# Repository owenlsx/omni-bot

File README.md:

# Omni Robot PCB

KiCad project for the Omni-directional robot.

## Contents
- Schematic: Omni_robot.kicad_sch
- PCB layout: Omni_robot.kicad_pcb

## Notes
- ESP32-S3 based controller
- BMX055 IMU
- 1S LiPo power system

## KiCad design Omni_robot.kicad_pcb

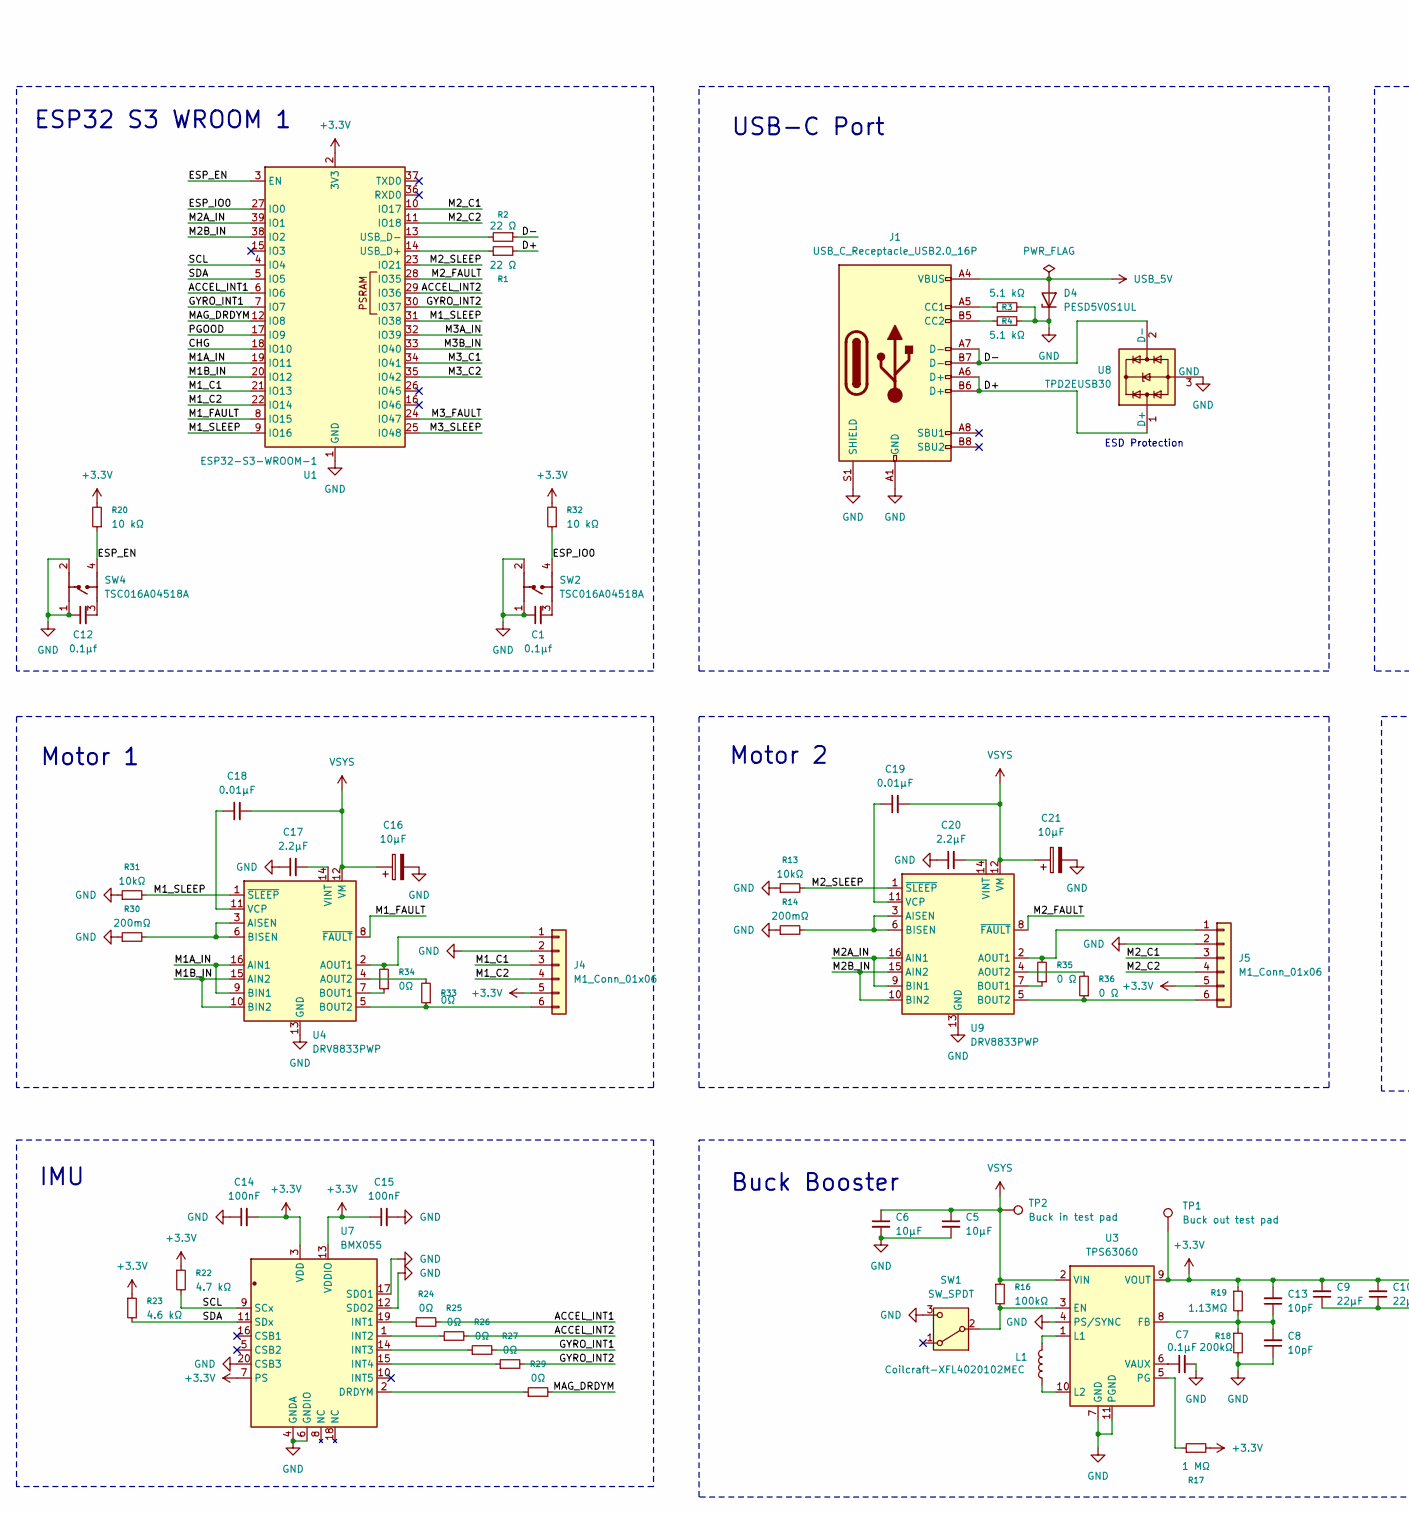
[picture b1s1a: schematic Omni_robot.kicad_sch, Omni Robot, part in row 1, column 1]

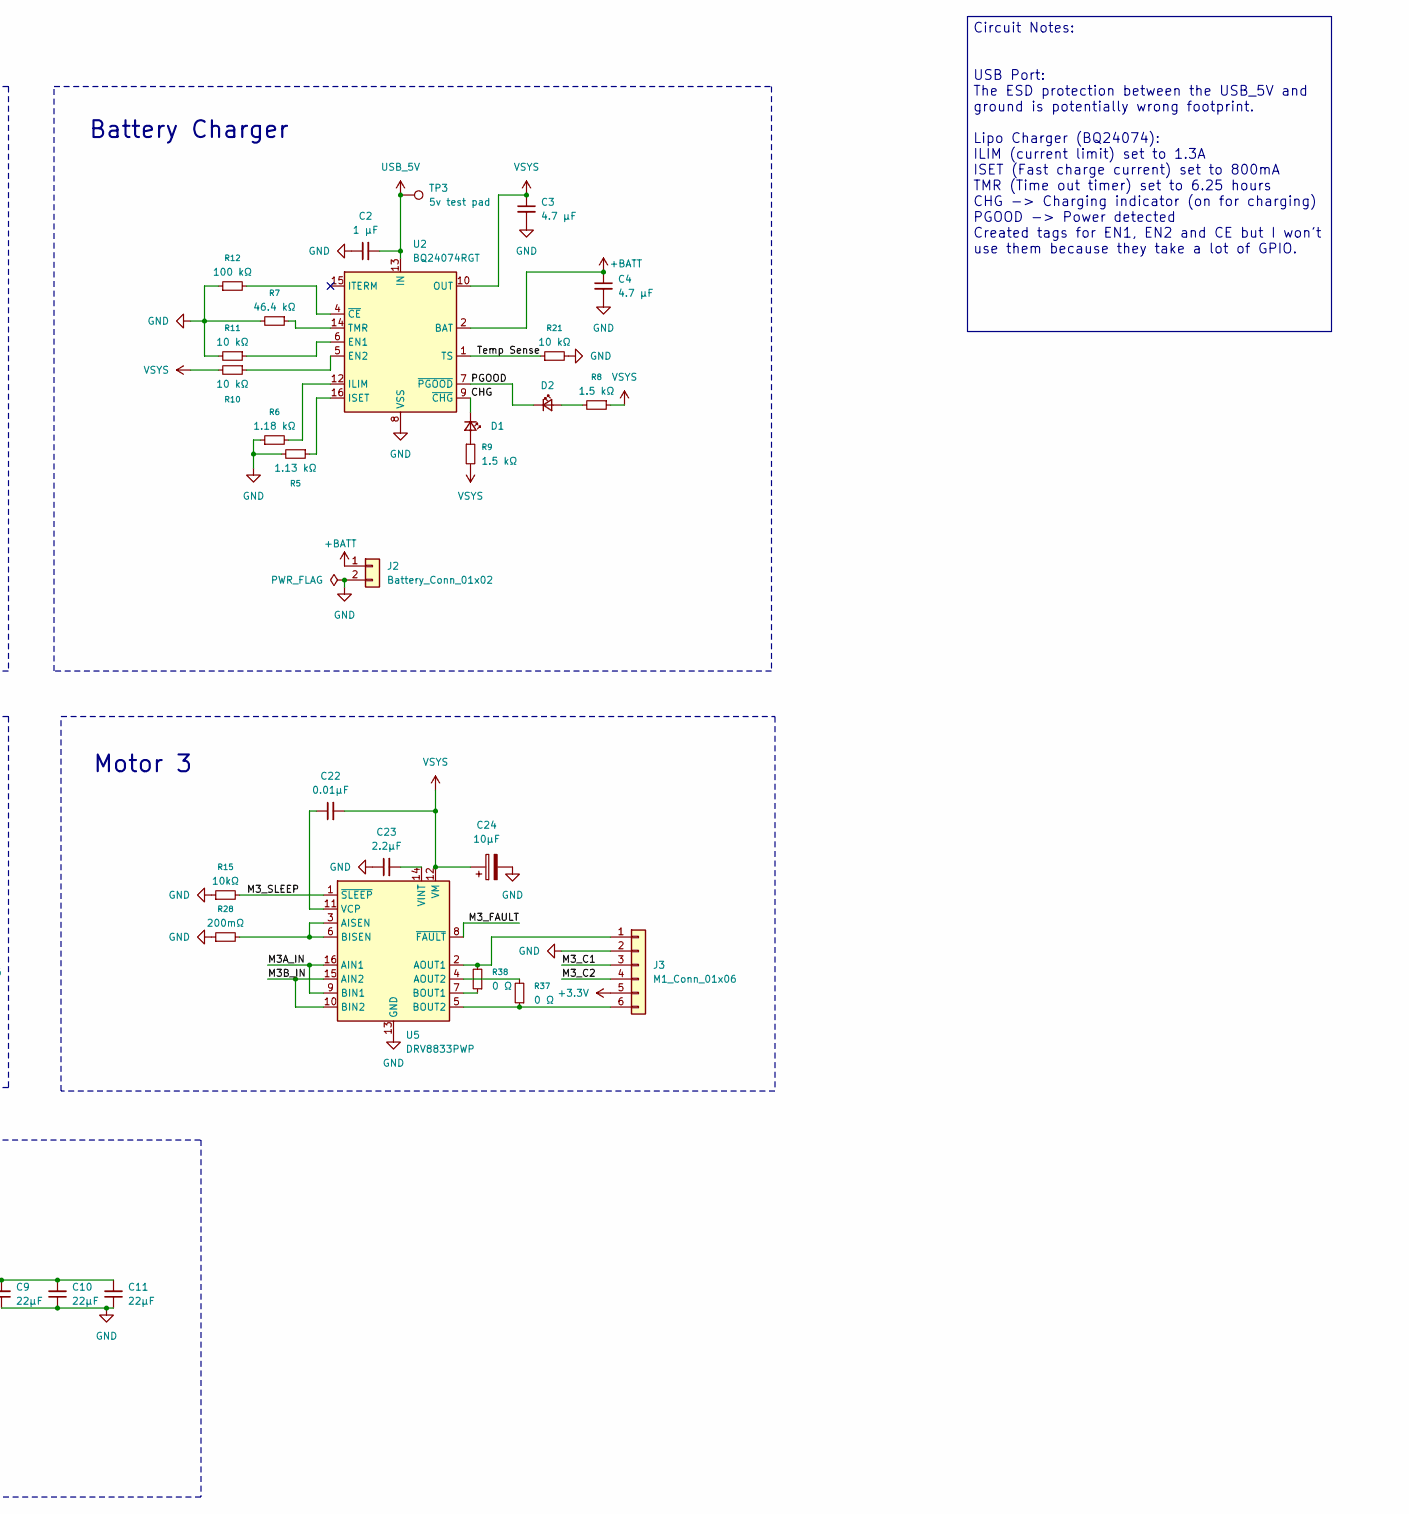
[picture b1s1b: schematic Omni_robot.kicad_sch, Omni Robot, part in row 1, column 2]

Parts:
C1, C12: 0.1µf; C_0603_1608Metric
C2: 1 µF; C_0603_1608Metric
C3, C4: 4.7 µF; C_0603_1608Metric
C5, C6, C16: 10µF; C_0603_1608Metric
C7: 0.1µF; C_0603_1608Metric
C8, C13: 10pF; C_0603_1608Metric
C9, C10, C11: 22µF; C_0603_1608Metric
C14, C15: 100nF; C_0603_1608Metric
C17: 2.2µF; C_0603_1608Metric
C18: 0.01µF; C_0603_1608Metric
C19, C22: 0.01µF; R_0603_1608Metric
C20, C23: 2.2µF; R_0603_1608Metric
C21, C24: 10µF; R_0603_1608Metric
D1, D2: LED_Small; R_0603_1608Metric
D4: PESD5V0S1UL; R_0603_1608Metric
J1: USB_C_Receptacle_USB2.0_16P; USB_C_Receptacle_Palconn_UTC16-G
J2: Battery_Conn_01x02; JST_PH_B2B-PH-K_1x02_P2.00mm_Vertical
J3, J4, J5: M1_Conn_01x06; JST_GH_BM06B-GHS-TBT_1x06-1MP_P1.25mm_Vertical
L1: Coilcraft-XFL4020102MEC; L_Coilcraft_XAL4020-XXX
R1, R2: 22 Ω; R_0603_1608Metric
R3, R4: 5.1 kΩ; R_0603_1608Metric
R5: 1.13 kΩ; R_0603_1608Metric
R6: 1.18 kΩ; R_0603_1608Metric
R7: 46.4 kΩ; R_0603_1608Metric
R8, R9: 1.5 kΩ; R_0603_1608Metric
R10, R11, R20, R21, R32: 10 kΩ; R_0603_1608Metric
R12: 100 kΩ; R_0603_1608Metric
R13, R15, R31: 10kΩ; R_0603_1608Metric
R14, R28, R30: 200mΩ; R_0603_1608Metric
R16: 100kΩ; R_0603_1608Metric
R17: 1 MΩ; R_0603_1608Metric
R18: 200kΩ; R_0603_1608Metric
R19: 1.13MΩ; R_0603_1608Metric
R22: 4.7 kΩ; R_0603_1608Metric
R23: 4.6 kΩ; R_0603_1608Metric
R24, R25, R26, R27, R29, R33, R34: 0Ω; R_0805_2012Metric
R35, R36, R37, R38: 0 Ω; R_0805_2012Metric
SW1: SW_SPDT; SW-TH_SS12D07VG4
SW2, SW4: TSC016A04518A; SW-TH_4P-L4.5-W4.5-P3.00-LS4.8; Manufacturer Part TSC016A04518A
TP1: Buck out test pad; TestPoint_Pad_D3.0mm
TP2: Buck in test pad; TestPoint_Pad_D3.0mm
TP3: 5v test pad; TestPoint_Pad_D3.0mm
U1: ESP32-S3-WROOM-1
U2: BQ24074RGT; VQFN-16-1EP_3x3mm_P0.5mm_EP1.6x1.6mm
U3: TPS63060; Texas_S-PWSON-N10_ThermalVias
U4, U5, U9: DRV8833PWP; HTSSOP-16-1EP_4.4x5mm_P0.65mm_EP3.4x5mm_Mask2.46x2.31mm_The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
U7: BMX055; BMX055_EasyEDA; Manufacturer Part BMX055
U8: TPD2EUSB30; Texas_DRT-3

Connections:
+3.3V: C9.2, C10.2, C11.2, C13.2, C14.2, C15.1, J3.5, J4.5, J5.5, R17.2, R19.1, R20.2, R22.1, R23.1, R32.2, TP1.1, U1.2 (3V3), U3.9 (VOUT), U7.3 (VDD), U7.7 (PS), U7.13 (VDDIO)
+BATT: C4.1, J2.1, U2.2 (BAT), U2.3 (BAT)
/ACCEL_INT1: R24.2, U1.6 (IO6)
/ACCEL_INT2: R25.2, U1.29 (IO36)
/CHG: D1.1 (K), U1.18 (IO10), U2.9 (~CHG)
/D+: J1.A6 (D+), J1.B6 (D+), R1.2, U8.1 (D+)
/D-: J1.A7 (D-), J1.B7 (D-), R2.1, U8.2 (D-)
/ESP_EN: R20.1, SW4.4, U1.3 (EN)
/ESP_IO0: R32.1, SW2.4, U1.27 (IO0)
/GYRO_INT1: R26.2, U1.7 (IO7)
/GYRO_INT2: R27.2, U1.30 (IO37)
/M1A_IN: U1.19 (IO11), U4.9 (BIN1), U4.16 (AIN1)
/M1B_IN: U1.20 (IO12), U4.10 (BIN2), U4.15 (AIN2)
/M1_C1: J4.3, U1.21 (IO13)
/M1_C2: J4.4, U1.22 (IO14)
/M1_FAULT: U1.8 (IO15), U4.8 (~FAULT)
/M1_SLEEP: R31.2, U1.9 (IO16), U1.31 (IO38), U4.1 (~SLEEP)
/M2A_IN: U1.39 (IO1), U9.9 (BIN1), U9.16 (AIN1)
/M2B_IN: U1.38 (IO2), U9.10 (BIN2), U9.15 (AIN2)
/M2_C1: J5.3, U1.10 (IO17)
/M2_C2: J5.4, U1.11 (IO18)
/M2_FAULT: U1.28 (IO35), U9.8 (~FAULT)
/M2_SLEEP: R13.2, U1.23 (IO21), U9.1 (~SLEEP)
/M3A_IN: U1.32 (IO39), U5.9 (BIN1), U5.16 (AIN1)
/M3B_IN: U1.33 (IO40), U5.10 (BIN2), U5.15 (AIN2)
/M3_C1: J3.3, U1.34 (IO41)
/M3_C2: J3.4, U1.35 (IO42)
/M3_FAULT: U1.24 (IO47), U5.8 (~FAULT)
/M3_SLEEP: R15.2, U1.25 (IO48), U5.1 (~SLEEP)
/MAG_DRDYM: R29.2, U1.12 (IO8)
/PGOOD: D2.1 (K), U1.17 (IO9), U2.7 (~PGOOD)
/SCL: R22.2, U1.4 (IO4), U7.9 (SCx)
/SDA: R23.2, U1.5 (IO5), U7.11 (SDx)
/Temp Sense: R21.1, U2.1 (TS)
GND: C1.1, C2.1, C3.2, C4.2, C5.2, C6.2, C7.2, C8.1, C9.1, C10.1, C11.1, C12.1, C14.1, C15.2, C16.2, C17.1, C20.1, C21.2, C23.1, C24.2, D4.1 (K), J1.A1 (GND), J1.A12 (GND), J1.B1 (GND), J1.B12 (GND), J1.S1 (SHIELD), J2.2, J3.2, J4.2, J5.2, R3.2, R4.2, R5.2, R6.1, R7.2, R11.2, R12.1, R13.1, R14.1, R15.1, R18.2, R21.2, R28.1, R30.1, R31.1, SW1.3 (C), SW2.1, SW2.2, SW4.1, SW4.2, U1.1 (GND), U1.40 (GND), U1.41 (GND), U2.8 (VSS), U2.17 (VSS), U3.4 (PS/SYNC), U3.7 (GND), U3.11 (PGND), U4.13 (GND), U4.17 (GND), U5.13 (GND), U5.17 (GND), U7.4 (GNDA), U7.6 (GNDIO), U7.12 (SDO2), U7.17 (SDO1), U7.20 (CSB3), U8.3 (GND), U9.13 (GND), U9.17 (GND)
unnamed: C1.2, SW2.3
unnamed: C12.2, SW4.3
unnamed: D1.2 (A), R9.1
unnamed: D2.2 (A), R8.2
unnamed: J1.A5 (CC1), R3.1
unnamed: J1.B5 (CC2), R4.1
unnamed: J3.1, R38.2, U5.2 (AOUT1)
unnamed: J3.6, R37.1, U5.5 (BOUT2)
unnamed: J4.1, R34.2, U4.2 (AOUT1)
unnamed: J4.6, R33.1, U4.5 (BOUT2)
unnamed: J5.1, R35.2, U9.2 (AOUT1)
unnamed: J5.6, R36.1, U9.5 (BOUT2)
unnamed: R16.2, SW1.2 (B), U3.3 (EN)
unnamed: R1.1, U1.14 (USB_D+)
unnamed: R2.2, U1.13 (USB_D-)
unnamed: R11.1, U2.6 (EN1)
unnamed: R10.1, U2.5 (EN2)
unnamed: R6.2, U2.12 (ILIM)
unnamed: R5.1, U2.16 (ISET)
unnamed: R7.1, U2.14 (TMR)
unnamed: R12.2, U2.4 (~CE)
unnamed: C8.2, C13.1, R18.1, R19.2, U3.8 (FB)
unnamed: L1.2, U3.1 (L1)
unnamed: L1.1, U3.10 (L2)
unnamed: R17.1, U3.5 (PG)
unnamed: C7.1, U3.6 (VAUX)
unnamed: R30.2, U4.3 (AISEN), U4.6 (BISEN)
unnamed: R33.2, U4.4 (AOUT2)
unnamed: R34.1, U4.7 (BOUT1)
unnamed: C18.1, U4.11 (VCP)
unnamed: C17.2, U4.14 (VINT)
unnamed: R28.2, U5.3 (AISEN), U5.6 (BISEN)
unnamed: R37.2, U5.4 (AOUT2)
unnamed: R38.1, U5.7 (BOUT1)
unnamed: C22.1, U5.11 (VCP)
unnamed: C23.2, U5.14 (VINT)
unnamed: R29.1, U7.2 (DRDYM)
unnamed: R24.1, U7.19 (INT1)
unnamed: R25.1, U7.1 (INT2)
unnamed: R26.1, U7.14 (INT3)
unnamed: R27.1, U7.15 (INT4)
unnamed: R14.2, U9.3 (AISEN), U9.6 (BISEN)
unnamed: R36.2, U9.4 (AOUT2)
unnamed: R35.1, U9.7 (BOUT1)
unnamed: C19.1, U9.11 (VCP)
unnamed: C20.2, U9.14 (VINT)
USB_5V: C2.2, D4.2 (A), J1.A4 (VBUS), J1.A9 (VBUS), J1.B4 (VBUS), J1.B9 (VBUS), TP3.1, U2.13 (IN)
VSYS: C3.1, C5.1, C6.1, C16.1, C18.2, C19.2, C21.1, C22.2, C24.1, R8.1, R9.2, R10.2, R16.1, TP2.1, U2.10 (OUT), U2.11 (OUT), U3.2 (VIN), U4.12 (VM), U5.12 (VM), U9.12 (VM)

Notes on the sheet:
ESD Protection
USB-C Port
IMU
Motor 3
ESP32 S3 WROOM 1
Motor 1
Battery Charger
Buck Booster
Motor 2
Circuit Notes: USB Port: The ESD protection between the USB_5V and ground is potentially wrong footprint. Lipo Charger (BQ24074): ILIM (current limit) set to 1.3A ISET (Fast charge current) set to 800mA TMR (Time out timer) set to 6.25 hours CHG -> Charging indicator (on for charging) PGOOD -> Powe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

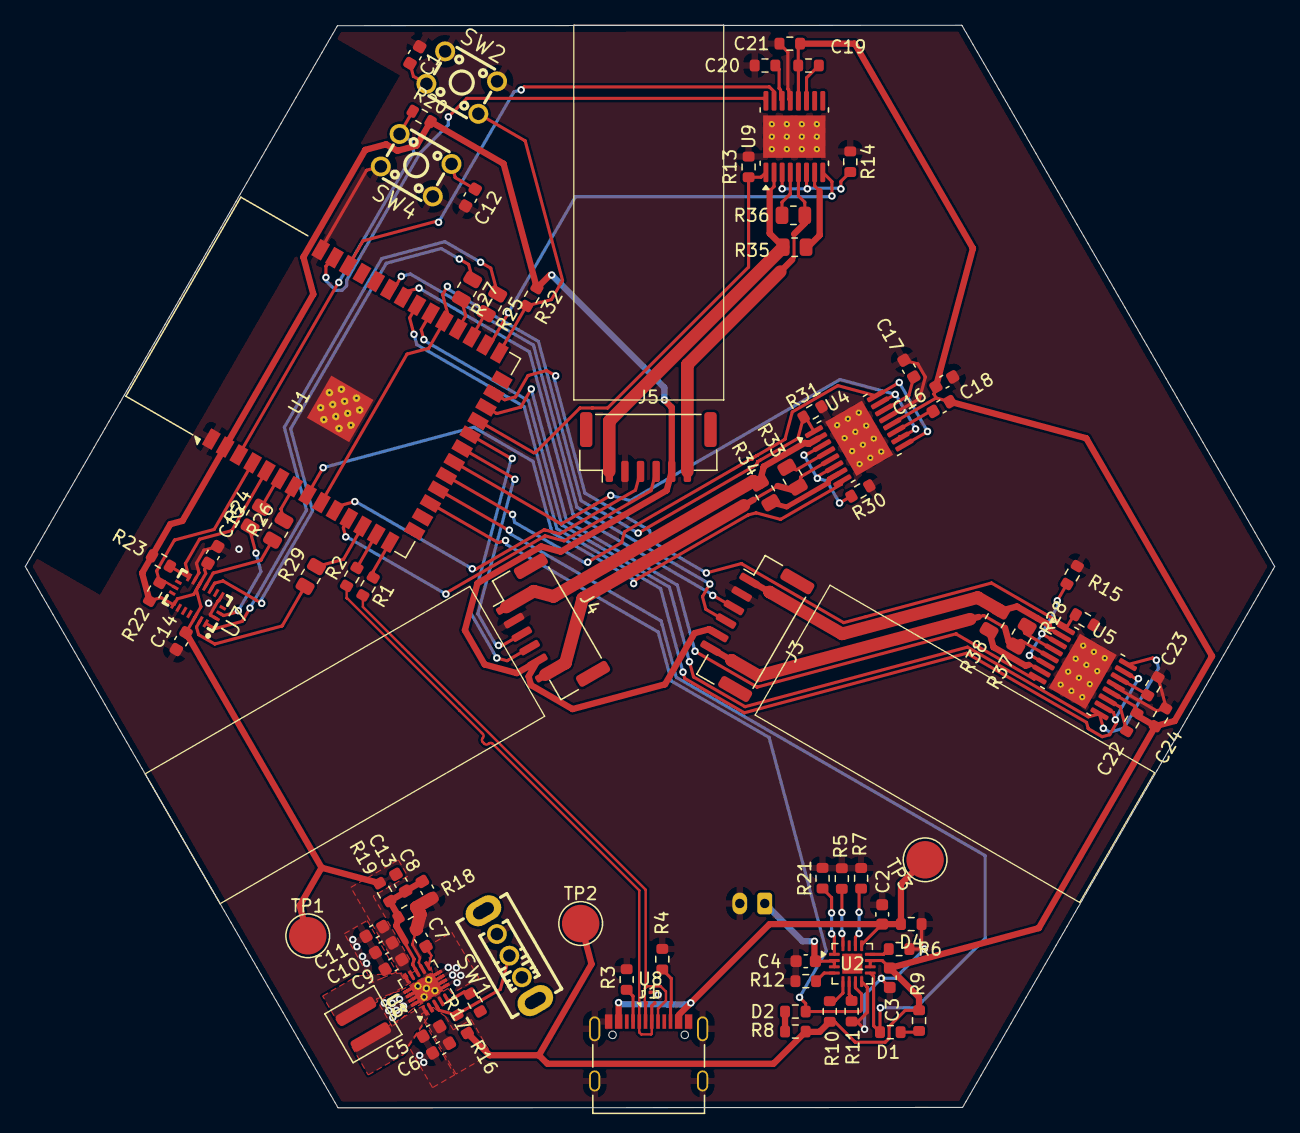
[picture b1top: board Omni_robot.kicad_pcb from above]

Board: 2 copper layers, 100.0 x 86.6 mm, 85 parts (1 on the bottom side), 83 nets.

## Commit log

2025-12-17 Initial KiCad project
2025-12-17 Added README file
2025-12-21 mostly finished schematic
2026-01-16 V1 schematic and basic layout
2026-01-19 Created tracks for motor power
2026-01-23 Finished basic tracing
